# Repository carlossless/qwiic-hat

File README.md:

# qwiic-hat

A simple low-profile Raspberry-Pi hat to connect Qwiic (3V3+I2C) devices

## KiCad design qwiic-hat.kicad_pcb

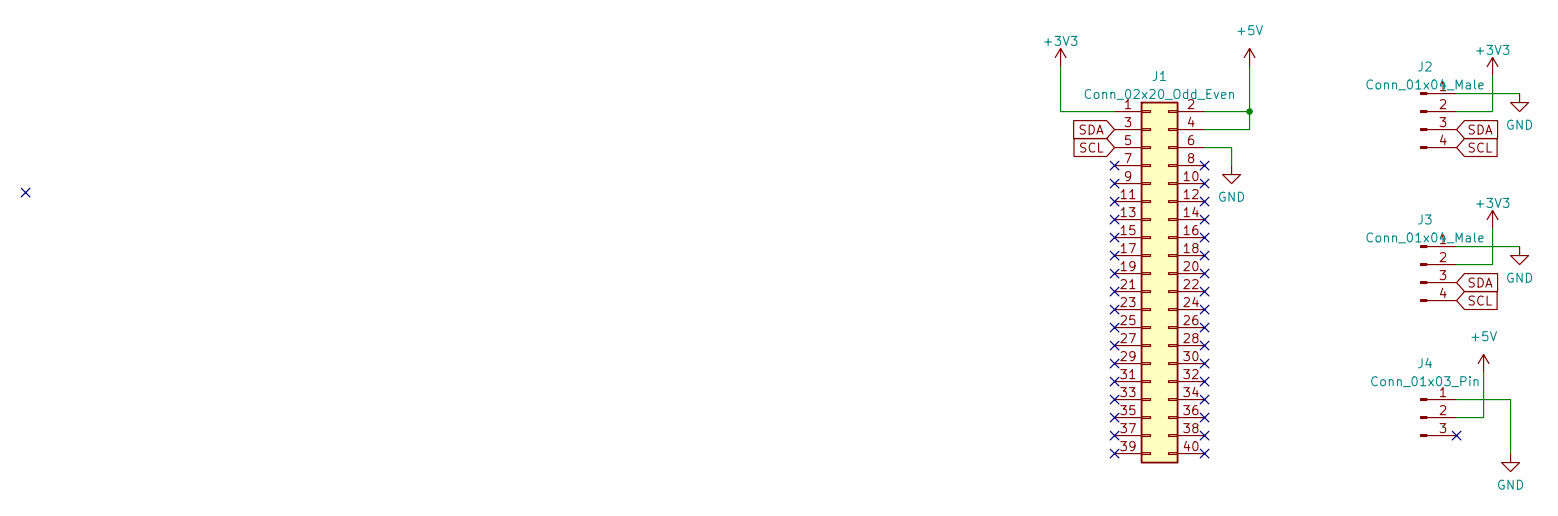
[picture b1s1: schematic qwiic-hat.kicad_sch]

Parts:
J1: Conn_02x20_Odd_Even; RPI_THROUGH_PIN_SOCKET
J2, J3: Conn_01x04_Male; JST_SH_SM04B-SRSS-TB_1x04-1MP_P1.00mm_Horizontal
J4: Conn_01x03_Pin; FanPinHeader_1x03_P2.54mm_Vertical

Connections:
+3V3: J1.1, J2.2, J3.2
+5V: J1.2, J1.4, J4.2
GND: J1.6, J2.1, J3.1, J4.1
PWM1: J1.33
SCL: J1.5, J2.4, J3.4
SDA: J1.3, J2.3, J3.3

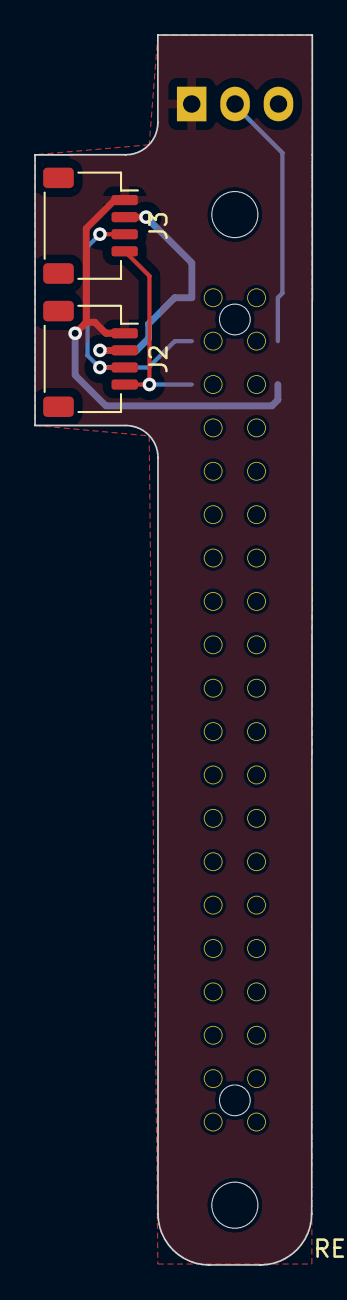
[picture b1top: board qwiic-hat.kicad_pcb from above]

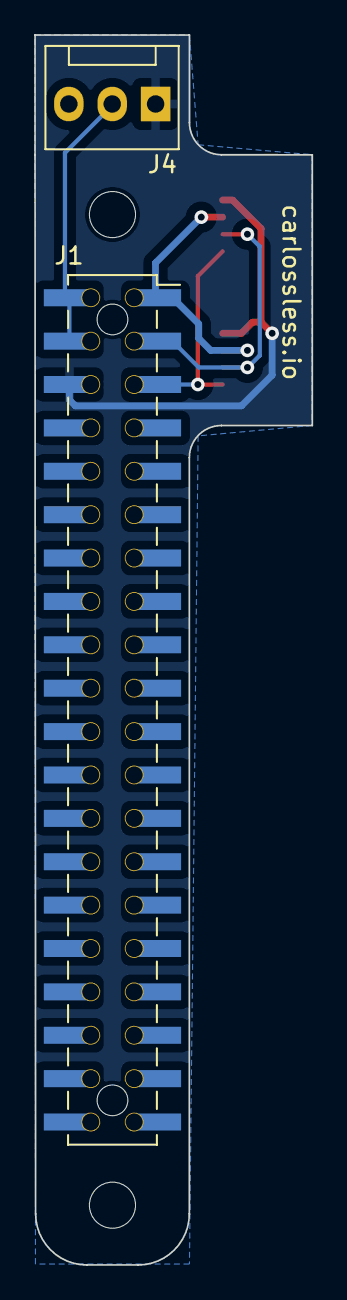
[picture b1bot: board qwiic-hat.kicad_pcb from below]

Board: 2 copper layers, 16.2 x 72.0 mm, 4 parts (2 on the bottom side), 5 nets.

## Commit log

2022-07-16 initial release
2023-08-06 added a 5v 3-pin header
2023-08-06 schematic cleanup
2025-03-09 cleanup sheets
